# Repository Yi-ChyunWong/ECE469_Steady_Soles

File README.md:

# ECE469Application

## Getting started

To make it easy for you to get started with GitLab, here's a list of recommended next steps.

Already a pro? Just edit this README.md and make it your own. Want to make it easy? [Use the template at the bottom](#editing-this-readme)!

## Add your files

- [ ] [Create](https://docs.gitlab.com/ee/user/project/repository/web_editor.html#create-a-file) or [upload](https://docs.gitlab.com/ee/user/project/repository/web_editor.html#upload-a-file) files
- [ ] [Add files using the command line](https://docs.gitlab.com/ee/gitlab-basics/add-file.html#add-a-file-using-the-command-line) or push an existing Git repository with the following command:

```
cd existing_repo
git remote add origin https://gitlab.oit.duke.edu/mka23/ece469application.git
git branch -M main
git push -uf origin main
```

## Integrate with your tools

- [ ] [Set up project integrations](https://gitlab.oit.duke.edu/mka23/ece469application/-/settings/integrations)

## Collaborate with your team

- [ ] [Invite team members and collaborators](https://docs.gitlab.com/ee/user/project/members/)
- [ ] [Create a new merge request](https://docs.gitlab.com/ee/user/project/merge_requests/creating_merge_requests.html)
- [ ] [Automatically close issues from merge requests](https://docs.gitlab.com/ee/user/project/issues/managing_issues.html#closing-issues-automatically)
- [ ] [Enable merge request approvals](https://docs.gitlab.com/ee/user/project/merge_requests/approvals/)
- [ ] [Set auto-merge](https://docs.gitlab.com/ee/user/project/merge_requests/merge_when_pipeline_succeeds.html)

## Test and Deploy

Use the built-in continuous integration in GitLab.

- [ ] [Get started with GitLab CI/CD](https://docs.gitlab.com/ee/ci/quick_start/index.html)
- [ ] [Analyze your code for known vulnerabilities with Static Application Security Testing (SAST)](https://docs.gitlab.com/ee/user/application_security/sast/)
- [ ] [Deploy to Kubernetes, Amazon EC2, or Amazon ECS using Auto Deploy](https://docs.gitlab.com/ee/topics/autodevops/requirements.html)
- [ ] [Use pull-based deployments for improved Kubernetes management](https://docs.gitlab.com/ee/user/clusters/agent/)
- [ ] [Set up protected environments](https://docs.gitlab.com/ee/ci/environments/protected_environments.html)

***

# Editing this README

When you're ready to make this README your own, just edit this file and use the handy template below (or feel free to structure it however you want - this is just a starting point!). Thanks to [makeareadme.com](https://www.makeareadme.com/) for this template.

## Suggestions for a good README

Every project is different, so consider which of these sections apply to yours. The sections used in the template are suggestions for most open source projects. Also keep in mind that while a README can be too long and detailed, too long is better than too short. If you think your README is too long, consider utilizing another form of documentation rather than cutting out information.

## Name
Choose a self-explaining name for your project.

## Description
Let people know what your project can do specifically. Provide context and add a link to any reference visitors might be unfamiliar with. A list of Features or a Background subsection can also be added here. If there are alternatives to your project, this is a good place to list differentiating factors.

## Badges
On some READMEs, you may see small images that convey metadata, such as whether or not all the tests are passing for the project. You can use Shields to add some to your README. Many services also have instructions for adding a badge.

## Visuals
Depending on what you are making, it can be a good idea to include screenshots or even a video (you'll frequently see GIFs rather than actual videos). Tools like ttygif can help, but check out Asciinema for a more sophisticated method.

## Installation
Within a particular ecosystem, there may be a common way of installing things, such as using Yarn, NuGet, or Homebrew. However, consider the possibility that whoever is reading your README is a novice and would like more guidance. Listing specific steps helps remove ambiguity and gets people to using your project as quickly as possible. If it only runs in a specific context like a particular programming language version or operating system or has dependencies that have to be installed manually, also add a Requirements subsection.

## Usage
Use examples liberally, and show the expected output if you can. It's helpful to have inline the smallest example of usage that you can demonstrate, while providing links to more sophisticated examples if they are too long to reasonably include in the README.

## Support
Tell people where they can go to for help. It can be any combination of an issue tracker, a chat room, an email address, etc.

## Roadmap
If you have ideas for releases in the future, it is a good idea to list them in the README.

## Contributing
State if you are open to contributions and what your requirements are for accepting them.

For people who want to make changes to your project, it's helpful to have some documentation on how to get started. Perhaps there is a script that they should run or some environment variables that they need to set. Make these steps explicit. These instructions could also be useful to your future self.

You can also document commands to lint the code or run tests. These steps help to ensure high code quality and reduce the likelihood that the changes inadvertently break something. Having instructions for running tests is especially helpful if it requires external setup, such as starting a Selenium server for testing in a browser.

## Authors and acknowledgment
Show your appreciation to those who have contributed to the project.

## License
For open source projects, say how it is licensed.

## Project status
If you have run out of energy or time for your project, put a note at the top of the README saying that development has slowed down or stopped completely. Someone may choose to fork your project or volunteer to step in as a maintainer or owner, allowing your project to keep going. You can also make an explicit request for maintainers.

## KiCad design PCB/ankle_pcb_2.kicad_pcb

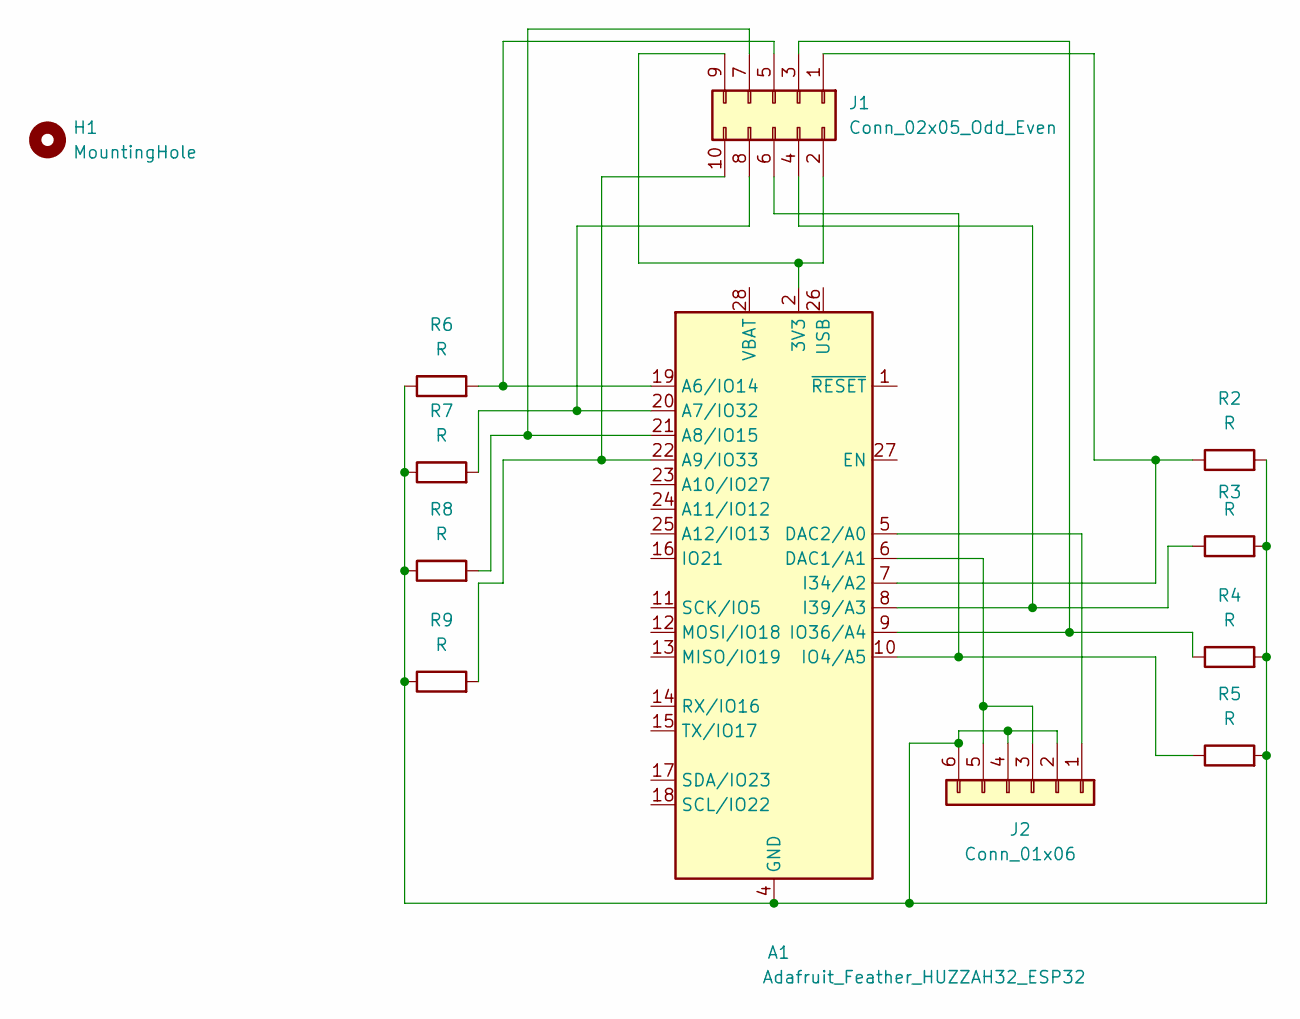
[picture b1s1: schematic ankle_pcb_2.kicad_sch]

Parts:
A1: Adafruit_Feather_HUZZAH32_ESP32; Adafruit_Feather
H1: MountingHole; MountingHole_2.5mm_Pad
J1: Conn_02x05_Odd_Even; PinHeader_2x05_P2.54mm_Horizontal
J2: Conn_01x06; PinHeader_1x06_P2.54mm_Horizontal
R2, R3, R4, R5, R6, R7, R8, R9: R; R_Box_L13.0mm_W4.0mm_P9.00mm

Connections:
unnamed: A1.2 (3V3), J1.2, J1.9
unnamed: A1.19 (A6/IO14), J1.5, R6.2
unnamed: A1.20 (A7/IO32), J1.8, R7.2
unnamed: A1.21 (A8/IO15), J1.7, R8.2
unnamed: A1.22 (A9/IO33), J1.10, R9.2
unnamed: A1.6 (DAC1/A1), J2.3, J2.5
unnamed: A1.5 (DAC2/A0), J2.1
unnamed: A1.4 (GND), J2.2, J2.4, J2.6, R2.2, R3.2, R4.2, R5.2, R6.1, R7.1, R8.1, R9.1
unnamed: A1.7 (I34/A2), J1.1, R2.1
unnamed: A1.8 (I39/A3), J1.4, R3.1
unnamed: A1.10 (IO4/A5), J1.6, R5.1
unnamed: A1.9 (IO36/A4), J1.3, R4.1

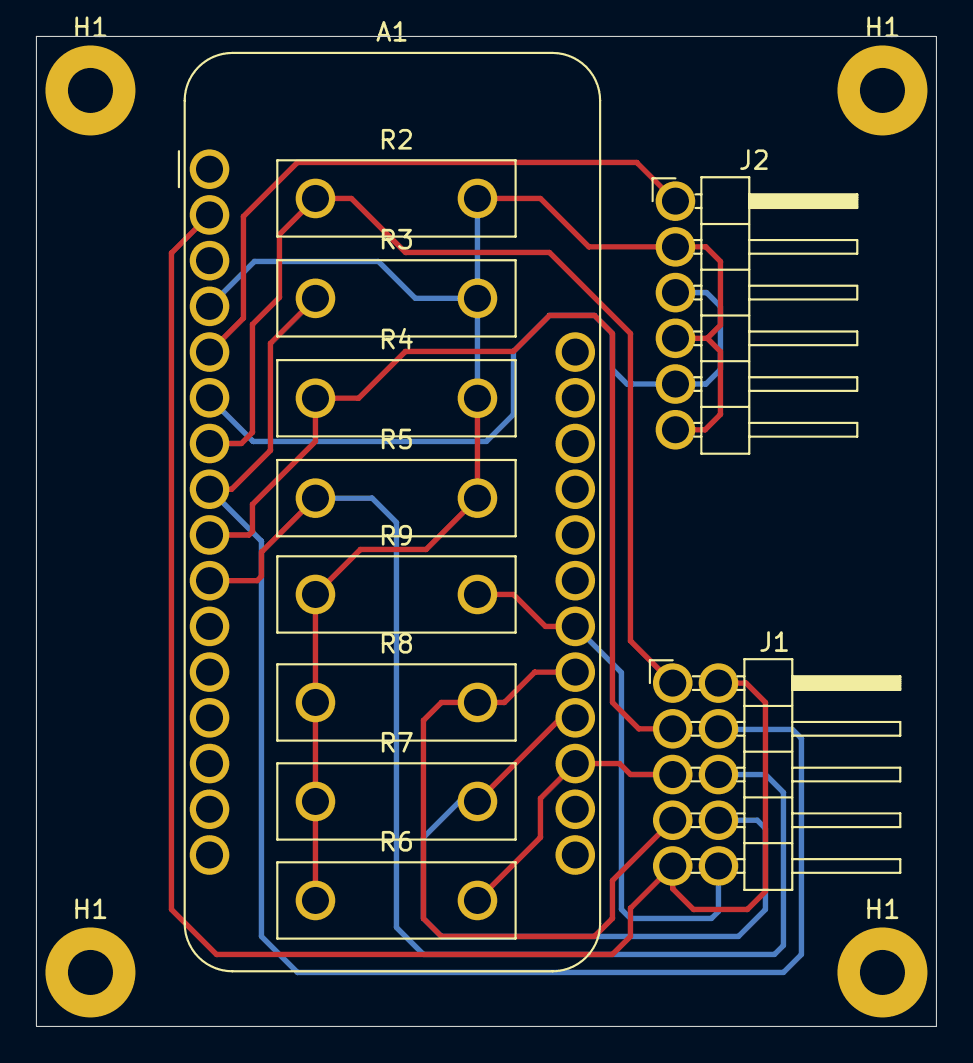
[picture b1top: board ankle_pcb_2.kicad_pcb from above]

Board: 2 copper layers, 50.0 x 55.0 mm, 15 parts (0 on the bottom side), 12 nets.

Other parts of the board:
H1#2, H1#3, H1#4: MountingHole; MountingHole_2.5mm_Pad

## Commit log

2025-03-06 Swift Heatmap Code
2025-03-06 Heatmap Code
2025-03-07 Added pressure sensor code to git
2025-03-20 Add skeleton bluetooth module
2025-03-26 send arduino data
2025-03-26 Integrated bluetooth and algorithm codes
2025-03-27 Fix bluetooth
2025-03-27 Heatmap showing
2025-03-27 Heatmap, Calibration, and Algorithm to Detect (still refining)
2025-04-02 Updated algorithm
2025-04-13 calibrate
2025-04-15 Move algorithm
2025-04-21 Add adjustable algorithm parameters
2026-04-29 Hardware
